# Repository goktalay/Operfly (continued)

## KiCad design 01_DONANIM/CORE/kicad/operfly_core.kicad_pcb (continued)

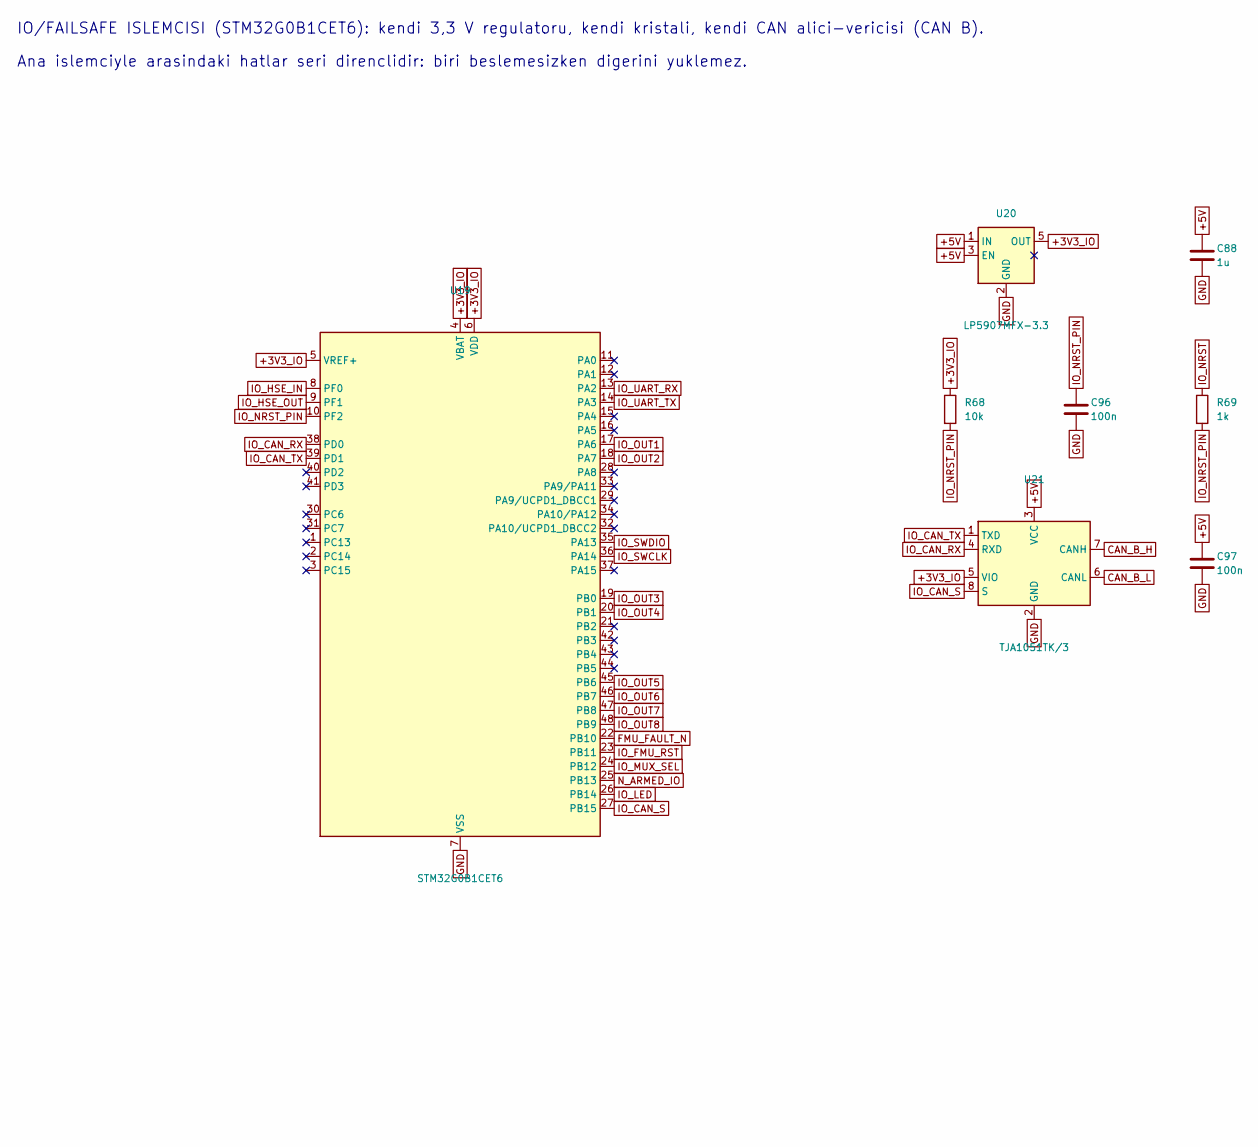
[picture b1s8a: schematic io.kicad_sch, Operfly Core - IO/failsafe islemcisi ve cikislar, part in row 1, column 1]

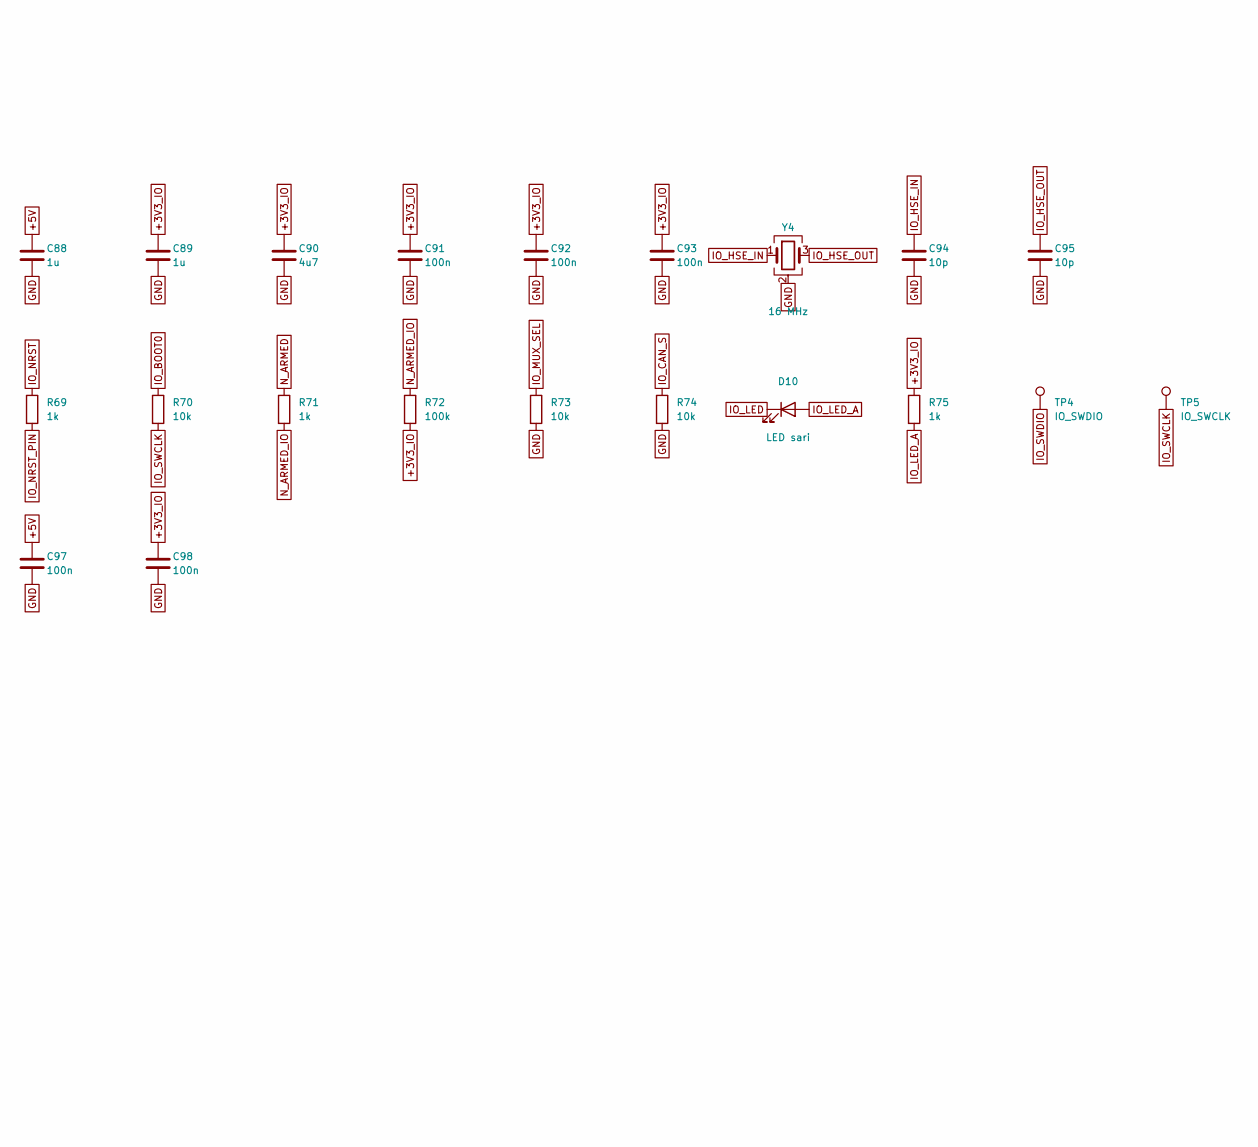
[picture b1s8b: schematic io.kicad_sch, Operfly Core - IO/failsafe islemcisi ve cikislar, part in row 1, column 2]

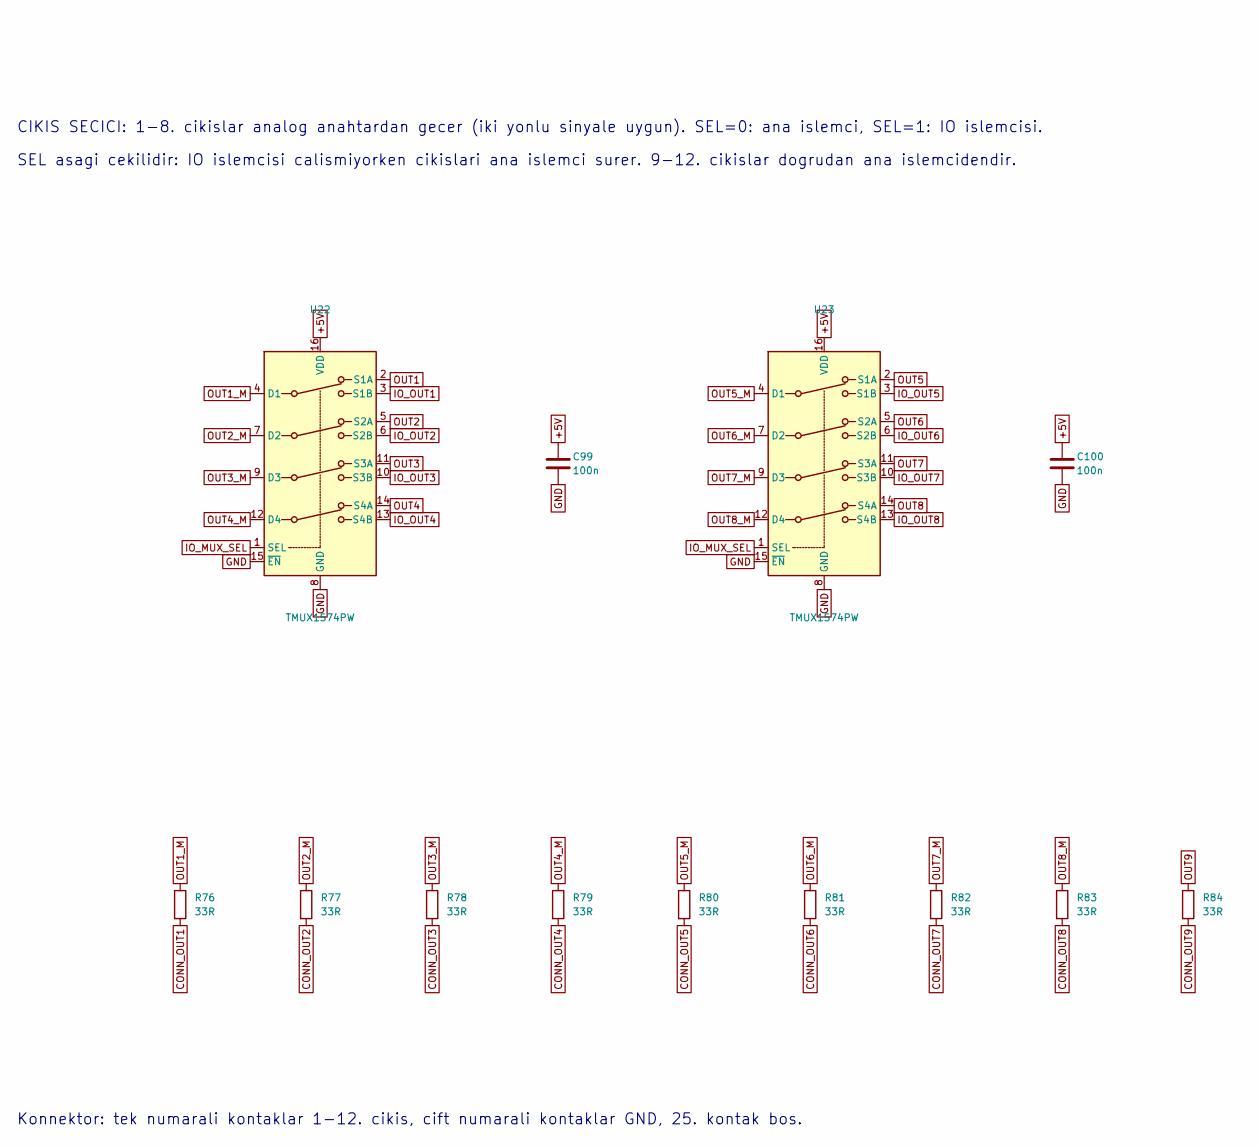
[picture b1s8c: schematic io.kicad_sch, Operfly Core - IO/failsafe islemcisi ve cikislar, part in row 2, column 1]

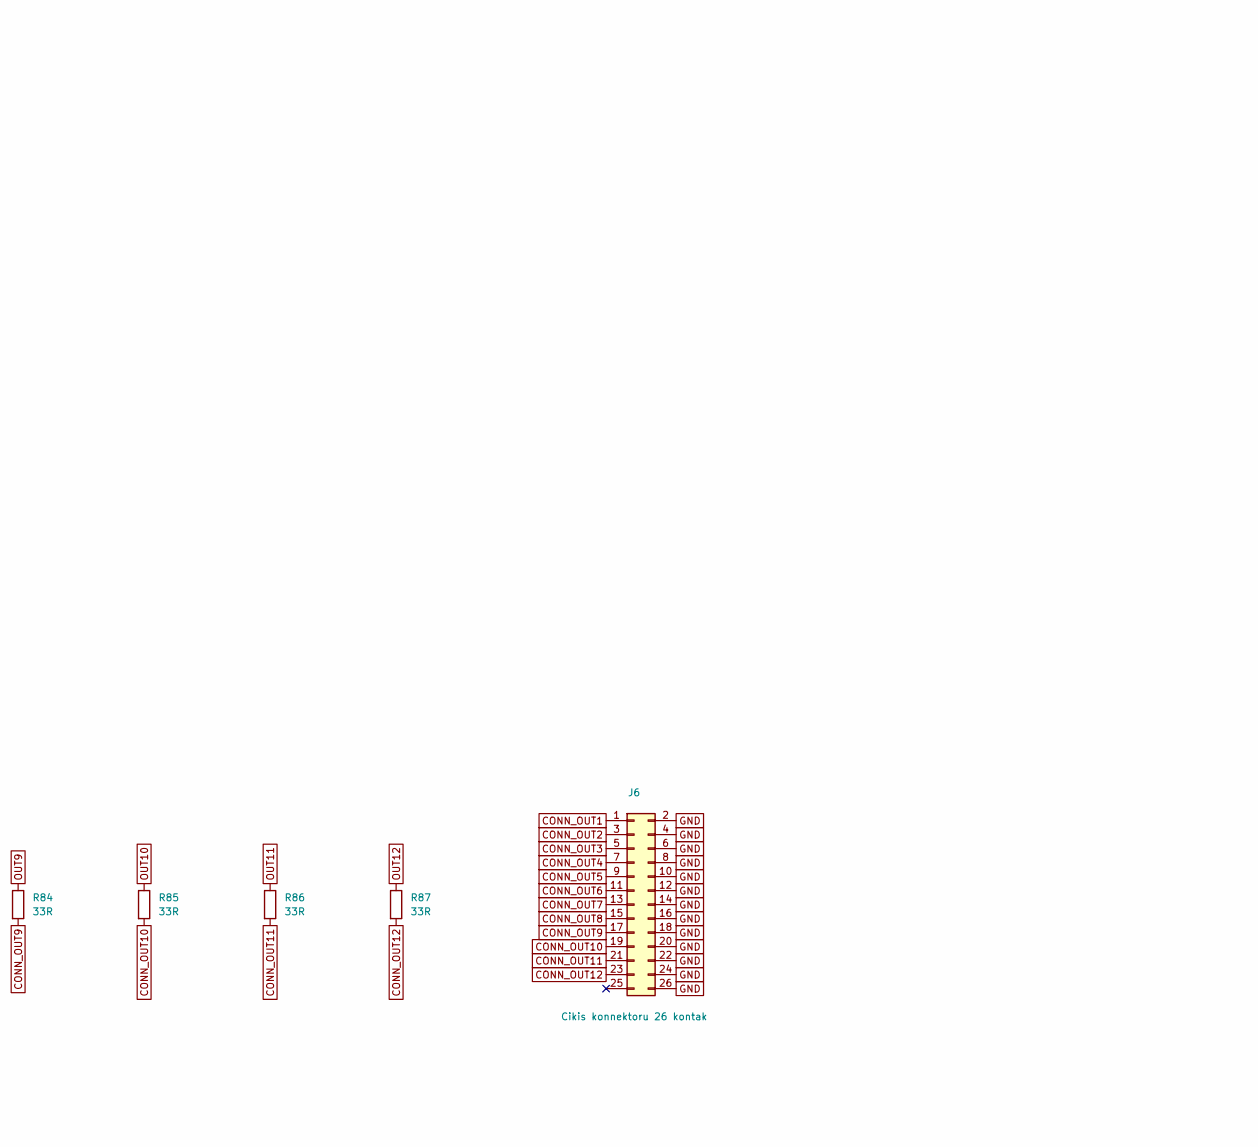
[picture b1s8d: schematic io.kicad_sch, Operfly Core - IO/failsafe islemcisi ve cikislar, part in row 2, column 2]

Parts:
C88, C89: 1u; C_0402_1005Metric
C90: 4u7; C_0603_1608Metric
C91, C92, C93, C96, C97, C98, C99, C100: 100n; C_0402_1005Metric
C94, C95: 10p; C_0402_1005Metric
D10: LED sari; LED_0603_1608Metric
J6: Cikis konnektoru 26 kontak; Harwin_Gecko_G125-MS12605M2P_2x13_P1.25mm_Vertical
R68, R70, R73, R74: 10k; R_0402_1005Metric
R69, R71, R75: 1k; R_0402_1005Metric
R72: 100k; R_0402_1005Metric
R76, R77, R78, R79, R80, R81, R82, R83, R84, R85, R86, R87: 33R; R_0402_1005Metric
TP4: IO_SWDIO; TestPoint_Pad_D1.0mm
TP5: IO_SWCLK; TestPoint_Pad_D1.0mm
U19: STM32G0B1CET6; LQFP-48_7x7mm_P0.5mm
U20: LP5907MFX-3.3; SOT-23-5
U21: TJA1051TK/3; HVSON-8-1EP_3x3mm_P0.65mm_EP1.6x2.4mm
U22, U23: TMUX1574PW; TSSOP-16_4.4x5mm_P0.65mm
Y4: 16 MHz; Crystal_SMD_3225-4Pin_3.2x2.5mm

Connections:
+3V3_IO: C89.1, C90.1, C91.1, C92.1, C93.1, C98.1, R68.1, R72.2, R75.1, U19.4 (VBAT), U19.5 (VREF+), U19.6 (VDD), U20.5 (OUT), U21.5 (VIO); also elsewhere on the board
+5V: C88.1, C97.1, C99.1, C100.1, U20.1 (IN), U20.3 (EN), U21.3 (VCC), U22.16 (VDD), U23.16 (VDD); also elsewhere on the board
CAN_B_H: U21.7 (CANH); also elsewhere on the board
CAN_B_L: U21.6 (CANL); also elsewhere on the board
CONN_OUT1: J6.1, R76.2
CONN_OUT2: J6.3, R77.2
CONN_OUT3: J6.5, R78.2
CONN_OUT4: J6.7, R79.2
CONN_OUT5: J6.9, R80.2
CONN_OUT6: J6.11, R81.2
CONN_OUT7: J6.13, R82.2
CONN_OUT8: J6.15, R83.2
CONN_OUT9: J6.17, R84.2
CONN_OUT10: J6.19, R85.2
CONN_OUT11: J6.21, R86.2
CONN_OUT12: J6.23, R87.2
FMU_FAULT_N: U19.22 (PB10); also elsewhere on the board
GND: C88.2, C89.2, C90.2, C91.2, C92.2, C93.2, C94.2, C95.2, C96.2, C97.2, C98.2, C99.2, C100.2, J6.2, J6.4, J6.6, J6.8, J6.10, J6.12, J6.14, J6.16, J6.18, J6.20, J6.22, J6.24, J6.26, R73.2, R74.2, U19.7 (VSS), U20.2 (GND), U21.2 (GND), U21.9 (GND), U22.8 (GND), U22.15 (~EN), U23.8 (GND), U23.15 (~EN), Y4.2 (G), Y4.4 (G); also elsewhere on the board
IO_BOOT0: R70.1; also elsewhere on the board
IO_CAN_RX: U19.38 (PD0), U21.4 (RXD)
IO_CAN_S: R74.1, U19.27 (PB15), U21.8 (S)
IO_CAN_TX: U19.39 (PD1), U21.1 (TXD)
IO_FMU_RST: U19.23 (PB11); also elsewhere on the board
IO_HSE_IN: C94.1, U19.8 (PF0), Y4.1
IO_HSE_OUT: C95.1, U19.9 (PF1), Y4.3
IO_LED: D10.1 (K), U19.26 (PB14)
IO_LED_A: D10.2 (A), R75.2
IO_MUX_SEL: R73.1, U19.24 (PB12), U22.1 (SEL), U23.1 (SEL)
IO_NRST: R69.1; also elsewhere on the board
IO_NRST_PIN: C96.1, R68.2, R69.2, U19.10 (PF2)
IO_OUT1: U19.17 (PA6), U22.3 (S1B)
IO_OUT2: U19.18 (PA7), U22.6 (S2B)
IO_OUT3: U19.19 (PB0), U22.10 (S3B)
IO_OUT4: U19.20 (PB1), U22.13 (S4B)
IO_OUT5: U19.45 (PB6), U23.3 (S1B)
IO_OUT6: U19.46 (PB7), U23.6 (S2B)
IO_OUT7: U19.47 (PB8), U23.10 (S3B)
IO_OUT8: U19.48 (PB9), U23.13 (S4B)
IO_SWCLK: R70.2, TP5.1, U19.36 (PA14)
IO_SWDIO: TP4.1, U19.35 (PA13)
IO_UART_RX: U19.13 (PA2); also elsewhere on the board
IO_UART_TX: U19.14 (PA3); also elsewhere on the board
N_ARMED: R71.1; also elsewhere on the board
N_ARMED_IO: R71.2, R72.1, U19.25 (PB13)
OUT1: U22.2 (S1A); also elsewhere on the board
OUT1_M: R76.1, U22.4 (D1)
OUT2: U22.5 (S2A); also elsewhere on the board
OUT2_M: R77.1, U22.7 (D2)
OUT3: U22.11 (S3A); also elsewhere on the board
OUT3_M: R78.1, U22.9 (D3)
OUT4: U22.14 (S4A); also elsewhere on the board
OUT4_M: R79.1, U22.12 (D4)
OUT5: U23.2 (S1A); also elsewhere on the board
OUT5_M: R80.1, U23.4 (D1)
OUT6: U23.5 (S2A); also elsewhere on the board
OUT6_M: R81.1, U23.7 (D2)
OUT7: U23.11 (S3A); also elsewhere on the board
OUT7_M: R82.1, U23.9 (D3)
OUT8: U23.14 (S4A); also elsewhere on the board
OUT8_M: R83.1, U23.12 (D4)
OUT9: R84.1; also elsewhere on the board
OUT10: R85.1; also elsewhere on the board
OUT11: R86.1; also elsewhere on the board
OUT12: R87.1; also elsewhere on the board

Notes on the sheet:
Ana islemciyle arasindaki hatlar seri direnclidir: biri beslemesizken digerini yuklemez.
CIKIS SECICI: 1-8. cikislar analog anahtardan gecer (iki yonlu sinyale uygun). SEL=0: ana islemci, SEL=1: IO islemcisi.
IO/FAILSAFE ISLEMCISI (STM32G0B1CET6): kendi 3,3 V regulatoru, kendi kristali, kendi CAN alici-vericisi (CAN B).
SEL asagi cekilidir: IO islemcisi calismiyorken cikislari ana islemci surer. 9-12. cikislar dogrudan ana islemcidendir.
Konnektor: tek numarali kontaklar 1-12. cikis, cift numarali kontaklar GND, 25. kontak bos.

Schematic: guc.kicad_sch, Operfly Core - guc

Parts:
C1, C3, C7: 10u 50V; C_1206_3216Metric
C2: 100n 50V; C_0603_1608Metric
C4, C8, C18, C20, C21, C22, C23, C24: 100n; C_0402_1005Metric
C5, C6, C9, C10: 22u 16V; C_1206_3216Metric
C11, C12, C13, C14, C15, C16, C17, C19: 1u; C_0402_1005Metric
D1, D2: B360A (60 V, 3 A); D_SMA
D3: SMBJ18A; D_SMB
FB1: BLM18PG221; L_0603_1608Metric
L1: 4u7 XAL4020-472; L_Coilcraft_XAL4020-XXX
L2: 3u3 XAL4020-332; L_Coilcraft_XAL4020-XXX
R1, R2, R3, R4, R5, R8: 100k; R_0402_1005Metric
R6: 10R; R_0402_1005Metric
R7: 0R; R_0402_1005Metric
R9, R10, R11, R12, R13, R14: 10k; R_0402_1005Metric
R15: 18k; R_0402_1005Metric
U2: AP63205QWU; TSOT-23-6
U3: AP63203QWU; TSOT-23-6
U4, U5, U6: LP5907MFX-3.3; SOT-23-5

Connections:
+3V3: C9.1, C10.1, FB1.1, L2.2, R7.1, U3.1 (FB); also elsewhere on the board
+3V3A: C17.1, C18.1, FB1.2, R6.1; also elsewhere on the board
+3V3_S1: C12.1, R12.1, U4.5 (OUT); also elsewhere on the board
+3V3_S2: C14.1, U5.5 (OUT); also elsewhere on the board
+3V3_S3: C16.1, U6.5 (OUT); also elsewhere on the board
+5V: C5.1, C6.1, C11.1, C13.1, C15.1, L1.2, R10.1, R14.1, U2.1 (FB), U4.1 (IN), U5.1 (IN), U6.1 (IN); also elsewhere on the board
+12V_BUS1: D1.2 (A); also elsewhere on the board
+12V_BUS2: D2.2 (A); also elsewhere on the board
+12V_IN: C1.1, C2.1, C3.1, C7.1, D1.1 (K), D2.1 (K), D3.1 (A1), R1.1, R2.1, R8.1, U2.3 (IN), U3.3 (IN); also elsewhere on the board
BST_3V3: C8.1, U3.6 (BST)
BST_5V: C4.1, U2.6 (BST)
EN_3V3: R2.2, U3.2 (EN)
EN_5V: R1.2, U2.2 (EN)
GND: C1.2, C2.2, C3.2, C5.2, C6.2, C7.2, C9.2, C10.2, C11.2, C12.2, C13.2, C14.2, C15.2, C16.2, C17.2, C18.2, C19.2, C20.2, C21.2, C22.2, C23.2, C24.2, D3.2 (A2), R3.2, R4.2, R5.2, R9.2, R11.2, R13.2, R15.2, U2.4 (GND), U3.4 (GND), U4.2 (GND), U5.2 (GND), U6.2 (GND); also elsewhere on the board
PGOOD_5V: R14.2, R15.1; also elsewhere on the board
SENS1_EN: R3.1, U4.3 (EN); also elsewhere on the board
SENS2_EN: R4.1, U5.3 (EN); also elsewhere on the board
SENS3_EN: R5.1, U6.3 (EN); also elsewhere on the board
SW_3V3: C8.2, L2.1, U3.5 (SW)
SW_5V: C4.2, L1.1, U2.5 (SW)
V3V3_SENS: C24.1, R12.2, R13.1; also elsewhere on the board
V5_SENS: C23.1, R10.2, R11.1; also elsewhere on the board
V12_BUS_SENS: C22.1, R8.2, R9.1; also elsewhere on the board
VBAT: C21.1, R7.2; also elsewhere on the board
VREF: C19.1, C20.1, R6.2; also elsewhere on the board

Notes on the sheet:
GIRIS: iki omurga portu diyotla birlestirilir (+12V_IN). Asiri gerilim diyotu 18 V.
ANALOG BESLEME ve REFERANS: +3V3A ferrit uzerinden, VREF 10 ohm uzerinden. VBAT +3V3'e bagli (yedek pil yok).
SENSOR BESLEMELERI: her IMU icin ayri, islemciden acilip kapatilan dusuk gurultulu regulator (LP5907-3.3).
3,3 V: AP63203 (sabit 3,3 V, 2 A). L 3,3 uH, cikis 2 x 22 uF. 12 V'tan dogrudan beslenir.
OLCUM BOLUCULERI: 12 V icin 11:1, 5 V ve sensor beslemesi icin 2:1. PGOOD_5V: 5 V varken yuksek.
5 V: AP63205 (sabit 5 V, 2 A, 1,1 MHz). Degerler uretici ornek devresinden: L 4,7 uH, cikis 2 x 22 uF.

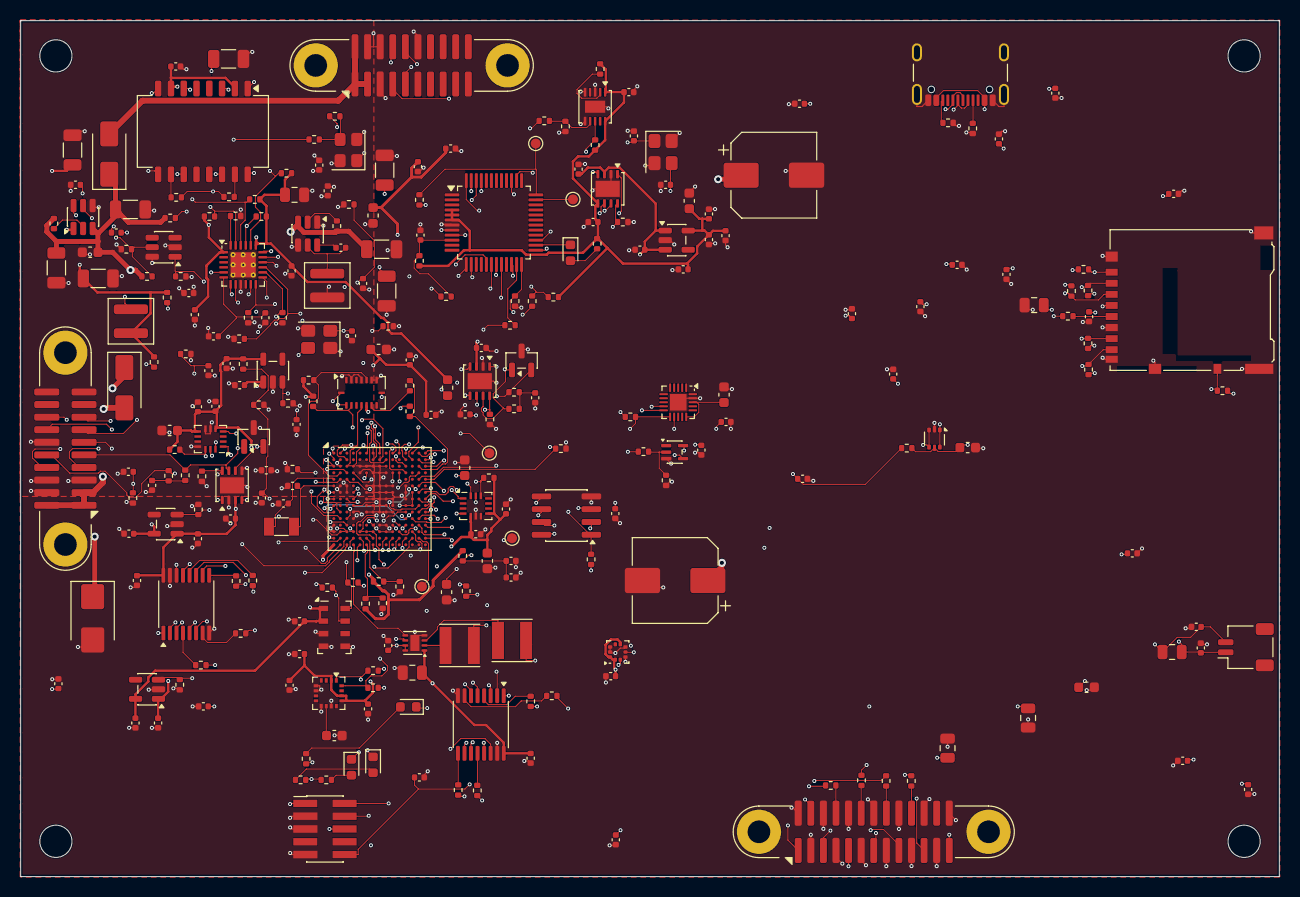
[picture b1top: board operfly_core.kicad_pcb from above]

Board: 6 copper layers, 125.0 x 85.0 mm, 268 parts (0 on the bottom side), 204 nets.

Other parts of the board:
H1, H2, H3, H4: M3; MountingHole_3.2mm_M3

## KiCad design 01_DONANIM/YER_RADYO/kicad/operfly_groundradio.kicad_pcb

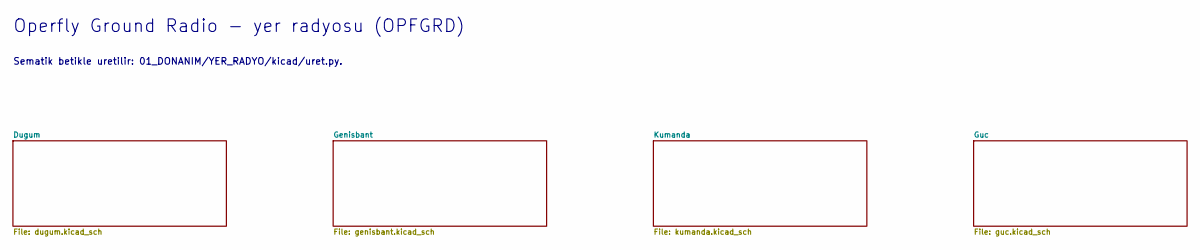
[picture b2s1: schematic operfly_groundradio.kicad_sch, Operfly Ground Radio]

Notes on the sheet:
Operfly Ground Radio - yer radyosu (OPFGRD)
Sematik betikle uretilir: 01_DONANIM/YER_RADYO/kicad/uret.py.

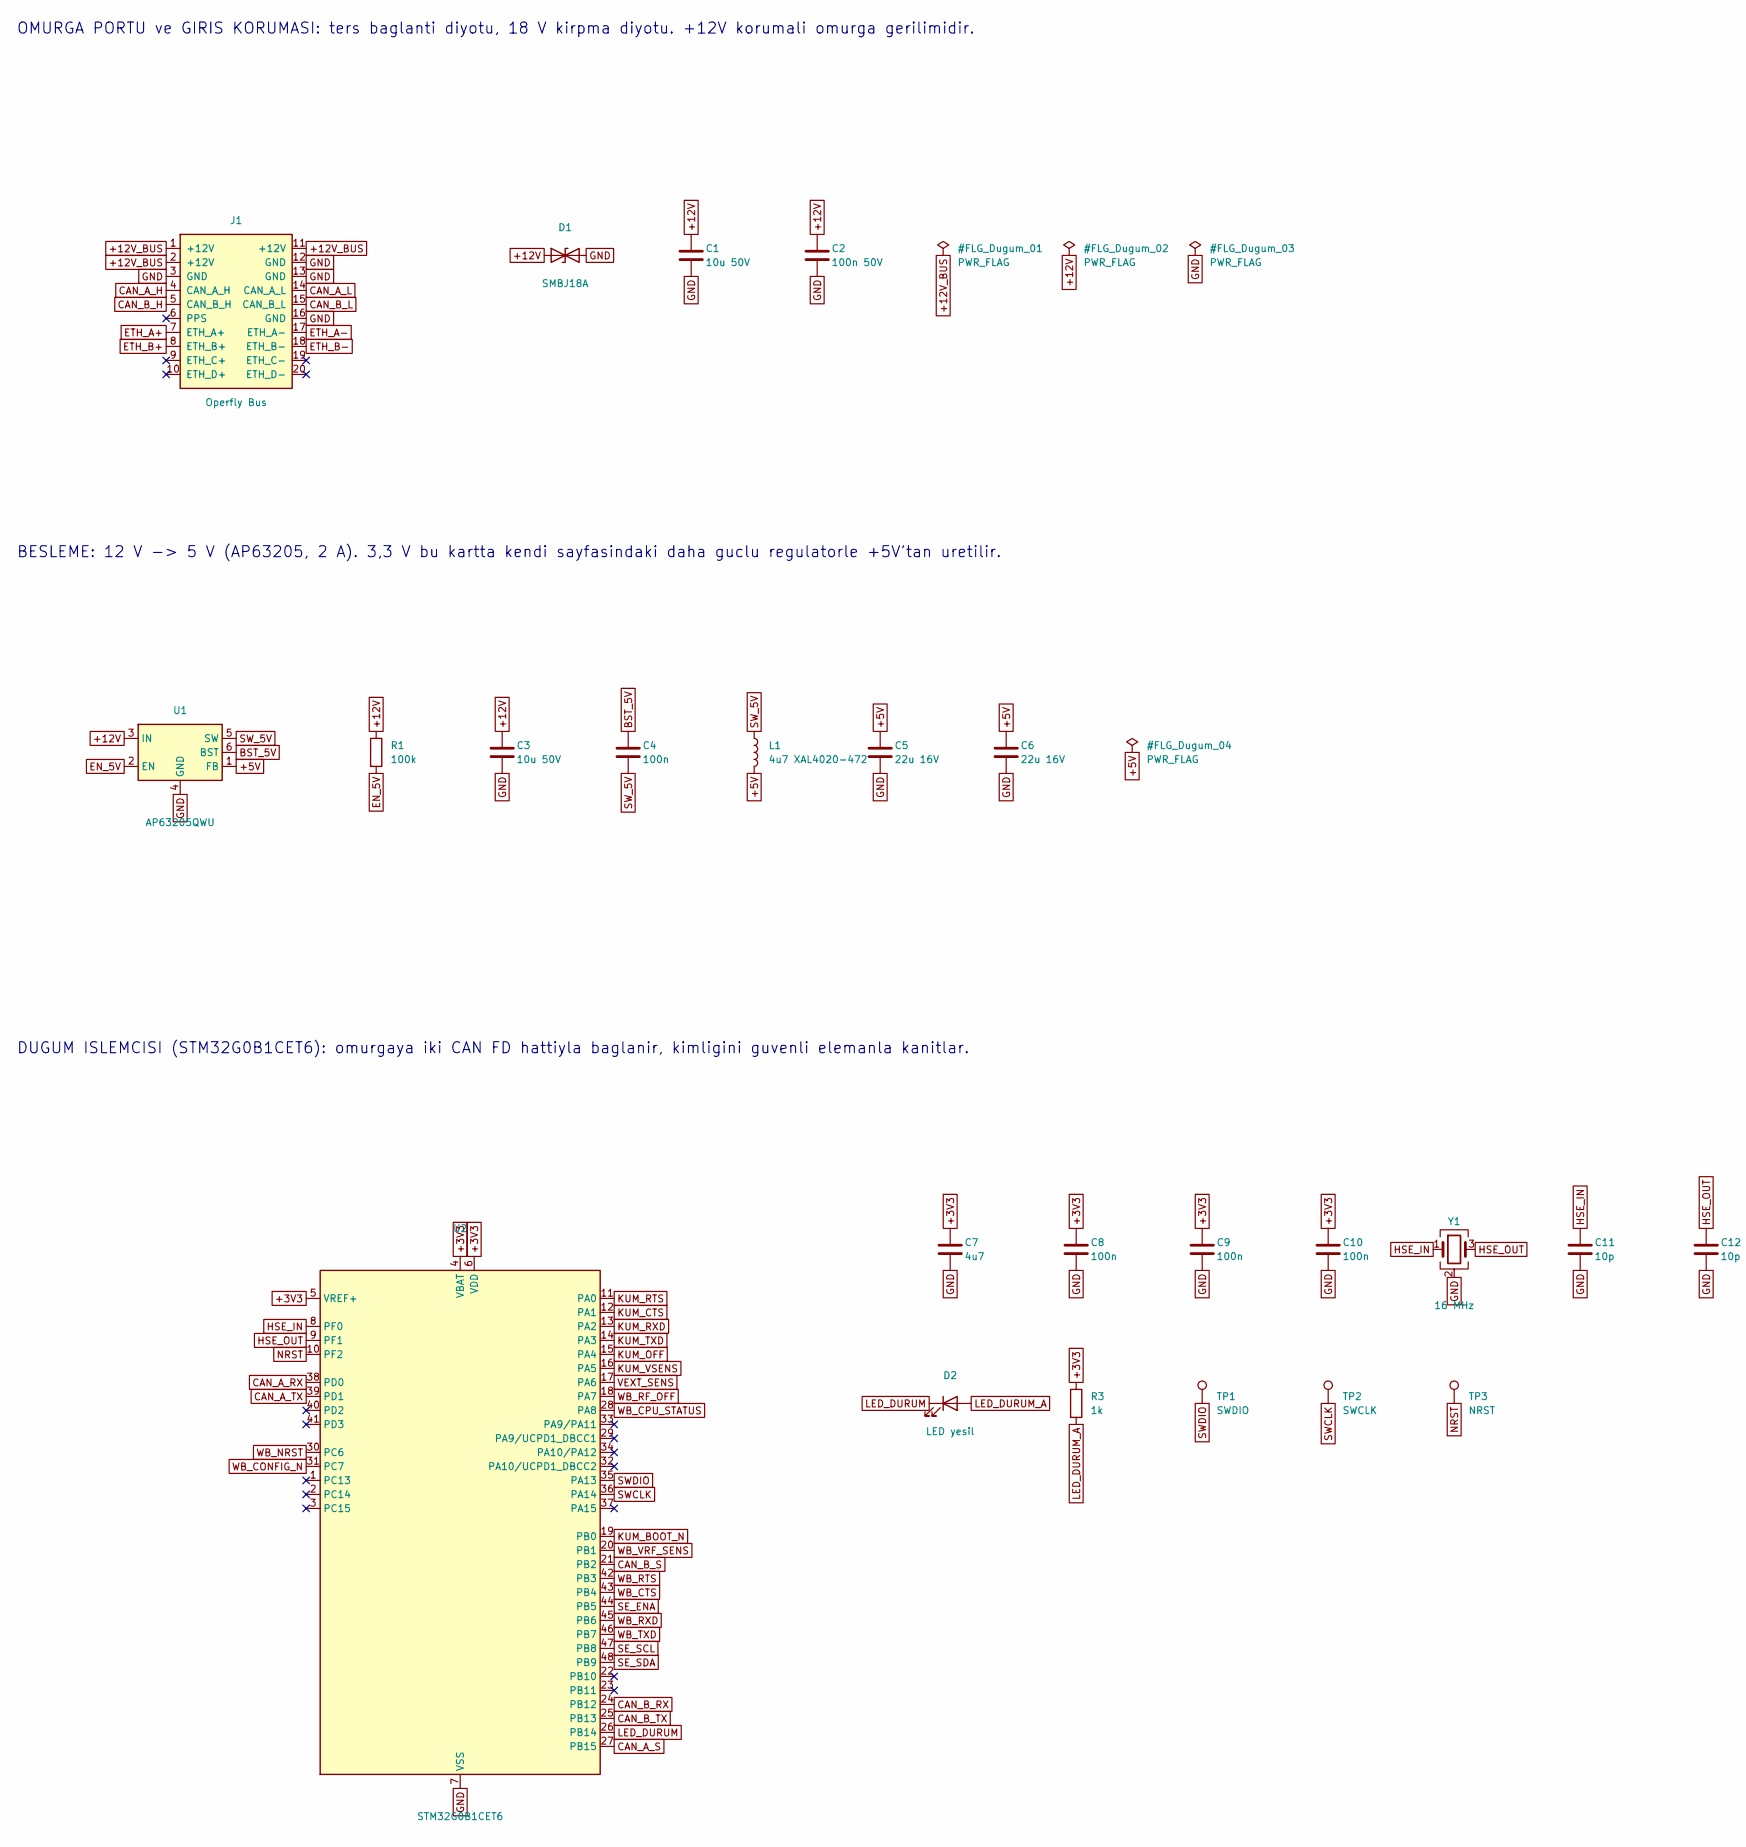
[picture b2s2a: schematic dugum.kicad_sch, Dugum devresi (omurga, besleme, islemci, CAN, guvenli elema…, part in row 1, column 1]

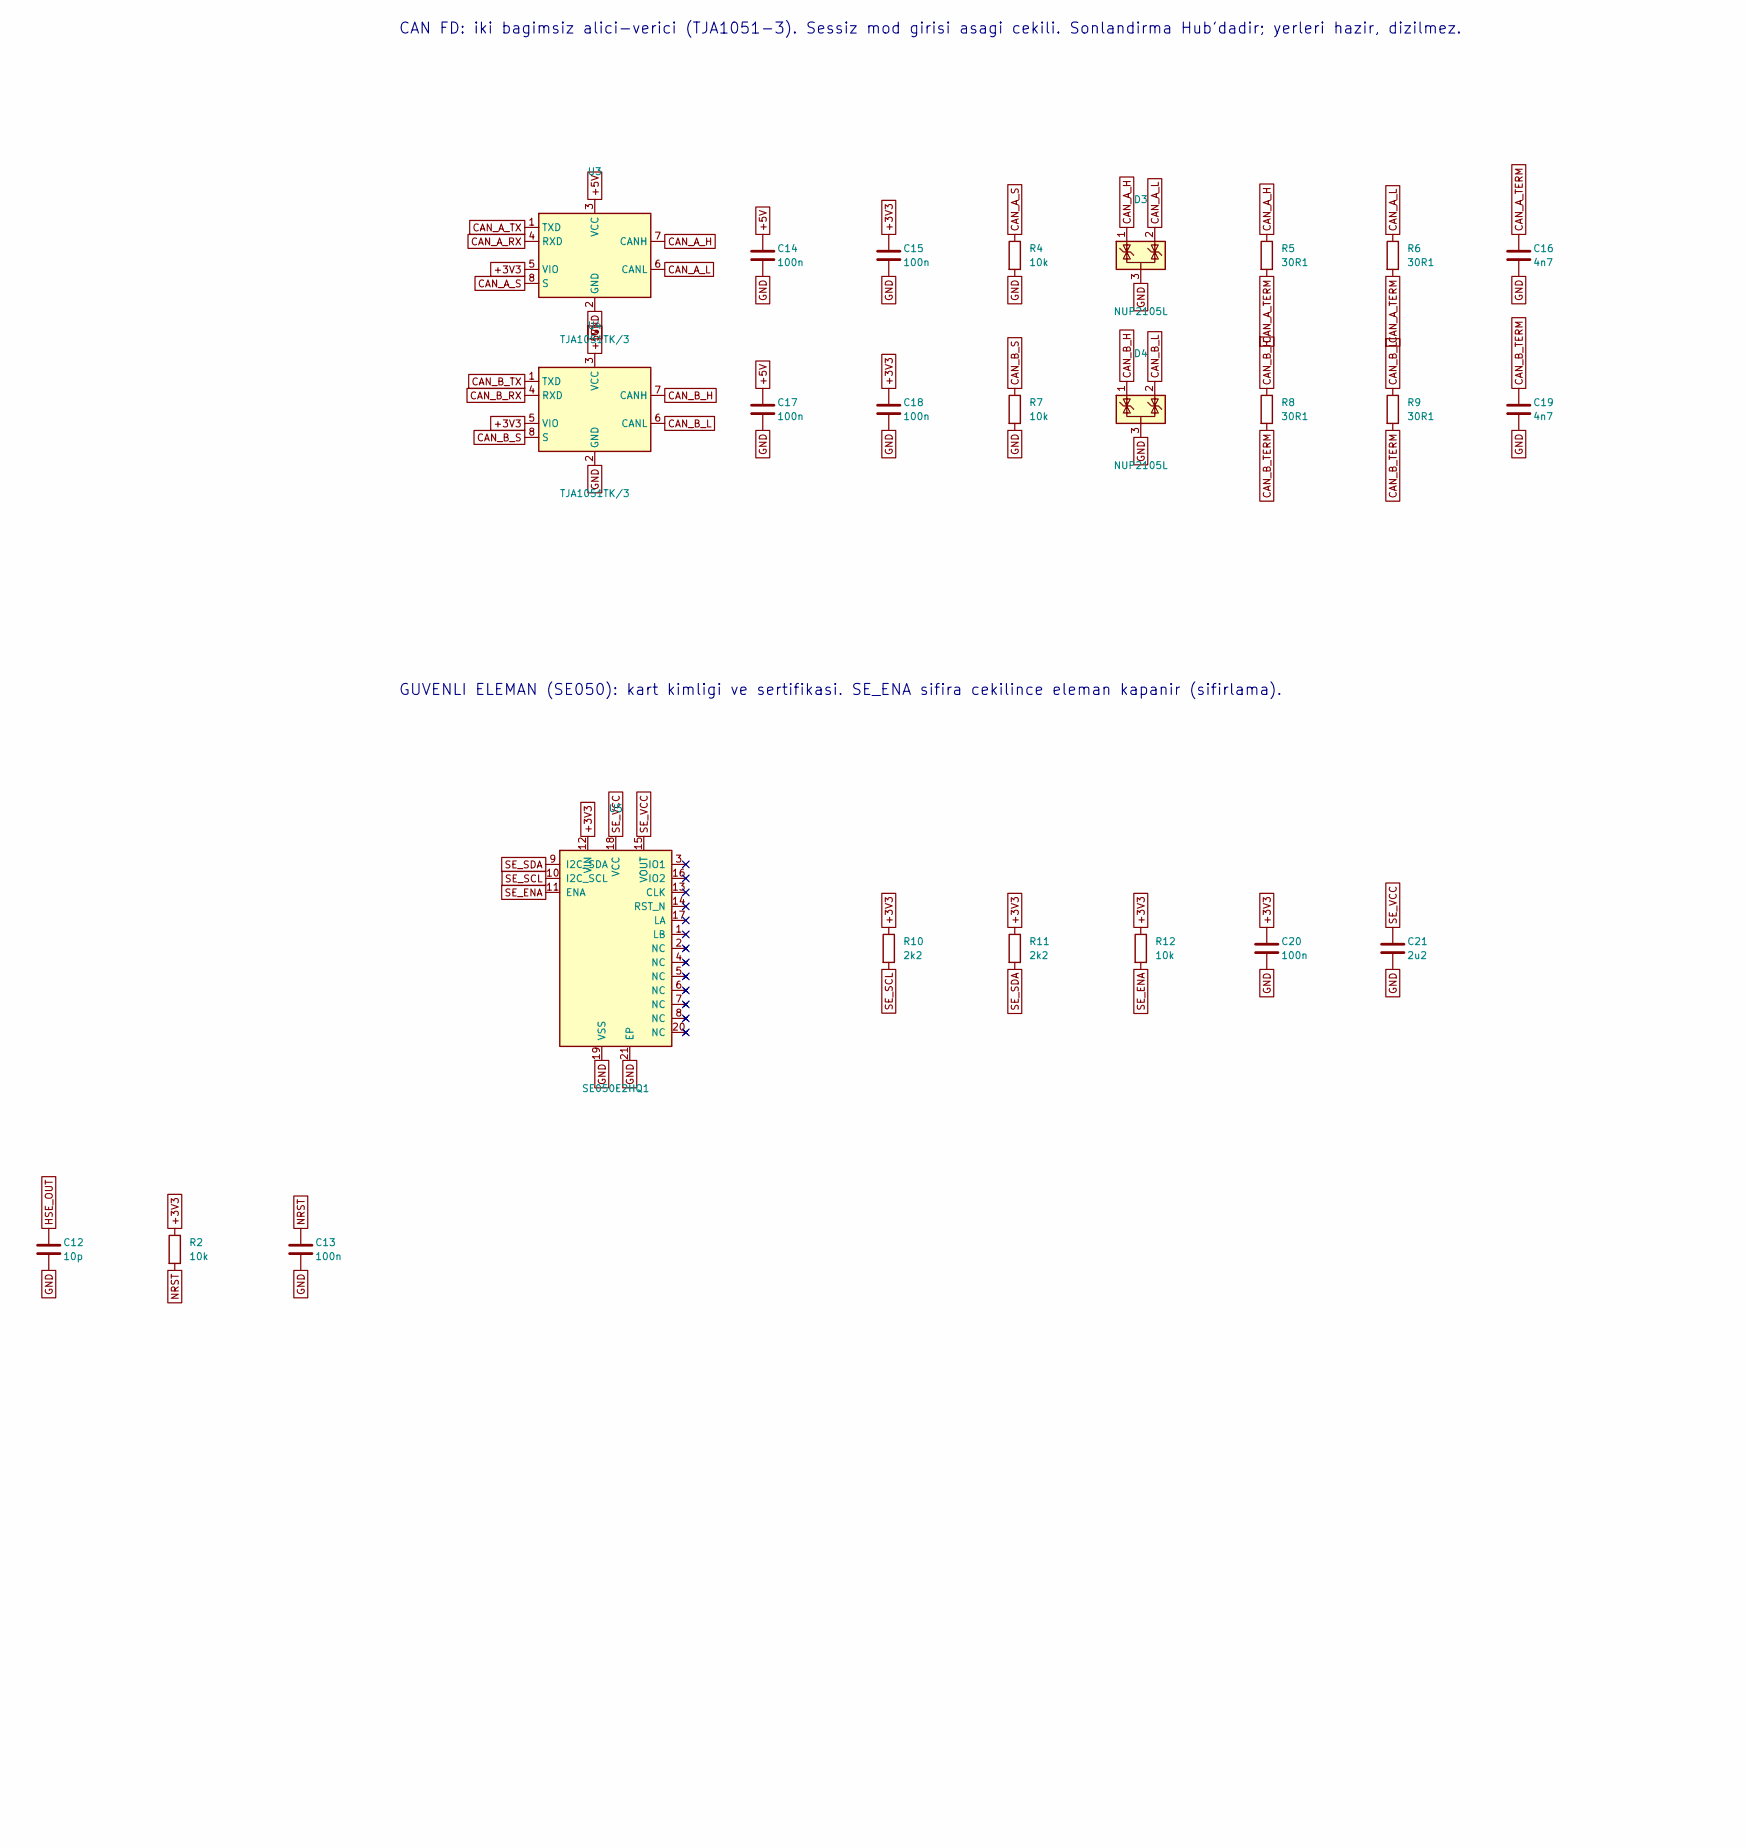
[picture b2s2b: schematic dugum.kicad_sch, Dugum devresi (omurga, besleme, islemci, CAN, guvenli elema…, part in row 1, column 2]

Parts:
C1, C3: 10u 50V; C_1206_3216Metric
C2: 100n 50V; C_0603_1608Metric
C4, C8, C9, C10, C13, C14, C15, C17, C18, C20: 100n; C_0402_1005Metric
C5, C6: 22u 16V; C_1206_3216Metric
C7: 4u7; C_0603_1608Metric
C11, C12: 10p; C_0402_1005Metric
C16, C19: 4n7; C_0402_1005Metric
C21: 2u2; C_0603_1608Metric
D1: SMBJ18A; D_SMB
D2: LED yesil; LED_0603_1608Metric
D3, D4: NUP2105L; SOT-23
J1: Operfly Bus; Harwin_Gecko_G125-MS12005M2P_2x10_P1.25mm_Vertical
L1: 4u7 XAL4020-472; L_Coilcraft_XAL4020-XXX
R1: 100k; R_0402_1005Metric
R2, R4, R7, R12: 10k; R_0402_1005Metric
R3: 1k; R_0402_1005Metric
R5, R6, R8, R9: 30R1; R_0402_1005Metric
R10, R11: 2k2; R_0402_1005Metric
TP1: SWDIO; TestPoint_Pad_D1.0mm
TP2: SWCLK; TestPoint_Pad_D1.0mm
TP3: NRST; TestPoint_Pad_D1.0mm
U1: AP63205QWU; TSOT-23-6
U2: STM32G0B1CET6; LQFP-48_7x7mm_P0.5mm
U3, U4: TJA1051TK/3; HVSON-8-1EP_3x3mm_P0.65mm_EP1.6x2.4mm
U5: SE050E2HQ1; QFN-20-1EP_3x3mm_P0.4mm_EP1.65x1.65mm
Y1: 16 MHz; Crystal_SMD_3225-4Pin_3.2x2.5mm

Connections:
+3V3: C7.1, C8.1, C9.1, C10.1, C15.1, C18.1, C20.1, R2.1, R3.1, R10.1, R11.1, R12.1, U2.4 (VBAT), U2.5 (VREF+), U2.6 (VDD), U3.5 (VIO), U4.5 (VIO), U5.12 (VIN); also elsewhere on the board
+5V: C5.1, C6.1, C14.1, C17.1, L1.2, U1.1 (FB), U3.3 (VCC), U4.3 (VCC)
+12V: C1.1, C2.1, C3.1, D1.1 (A1), R1.1, U1.3 (IN); also elsewhere on the board
+12V_BUS: J1.1 (+12V), J1.2 (+12V), J1.11 (+12V); also elsewhere on the board
BST_5V: C4.1, U1.6 (BST)
CAN_A_H: D3.1 (K), J1.4 (CAN_A_H), R5.1, U3.7 (CANH); also elsewhere on the board
CAN_A_L: D3.2 (K), J1.14 (CAN_A_L), R6.1, U3.6 (CANL); also elsewhere on the board
CAN_A_RX: U2.38 (PD0), U3.4 (RXD)
CAN_A_S: R4.1, U2.27 (PB15), U3.8 (S)
CAN_A_TERM: C16.1, R5.2, R6.2
CAN_A_TX: U2.39 (PD1), U3.1 (TXD)
CAN_B_H: D4.1 (K), J1.5 (CAN_B_H), R8.1, U4.7 (CANH); also elsewhere on the board
CAN_B_L: D4.2 (K), J1.15 (CAN_B_L), R9.1, U4.6 (CANL); also elsewhere on the board
CAN_B_RX: U2.24 (PB12), U4.4 (RXD)
CAN_B_S: R7.1, U2.21 (PB2), U4.8 (S)
CAN_B_TERM: C19.1, R8.2, R9.2
CAN_B_TX: U2.25 (PB13), U4.1 (TXD)
EN_5V: R1.2, U1.2 (EN)
ETH_A+: J1.7 (ETH_A+); also elsewhere on the board
ETH_A-: J1.17 (ETH_A-); also elsewhere on the board
ETH_B+: J1.8 (ETH_B+); also elsewhere on the board
ETH_B-: J1.18 (ETH_B-); also elsewhere on the board
GND: C1.2, C2.2, C3.2, C5.2, C6.2, C7.2, C8.2, C9.2, C10.2, C11.2, C12.2, C13.2, C14.2, C15.2, C16.2, C17.2, C18.2, C19.2, C20.2, C21.2, D1.2 (A2), D3.3 (A), D4.3 (A), J1.3 (GND), J1.12 (GND), J1.13 (GND), J1.16 (GND), R4.2, R7.2, U1.4 (GND), U2.7 (VSS), U3.2 (GND), U3.9 (GND), U4.2 (GND), U4.9 (GND), U5.19 (VSS), U5.21 (EP), Y1.2 (G), Y1.4 (G); also elsewhere on the board
HSE_IN: C11.1, U2.8 (PF0), Y1.1
HSE_OUT: C12.1, U2.9 (PF1), Y1.3
KUM_BOOT_N: U2.19 (PB0); also elsewhere on the board
KUM_CTS: U2.12 (PA1); also elsewhere on the board
KUM_OFF: U2.15 (PA4); also elsewhere on the board
KUM_RTS: U2.11 (PA0); also elsewhere on the board
KUM_RXD: U2.13 (PA2); also elsewhere on the board
KUM_TXD: U2.14 (PA3); also elsewhere on the board
KUM_VSENS: U2.16 (PA5); also elsewhere on the board
LED_DURUM: D2.1 (K), U2.26 (PB14)
LED_DURUM_A: D2.2 (A), R3.2
NRST: C13.1, R2.2, TP3.1, U2.10 (PF2)
SE_ENA: R12.2, U2.44 (PB5), U5.11 (ENA)
SE_SCL: R10.2, U2.47 (PB8), U5.10 (I2C_SCL)
SE_SDA: R11.2, U2.48 (PB9), U5.9 (I2C_SDA)
SE_VCC: C21.1, U5.15 (VOUT), U5.18 (VCC)
SWCLK: TP2.1, U2.36 (PA14)
SWDIO: TP1.1, U2.35 (PA13)
SW_5V: C4.2, L1.1, U1.5 (SW)
VEXT_SENS: U2.17 (PA6); also elsewhere on the board
WB_CONFIG_N: U2.31 (PC7); also elsewhere on the board
WB_CPU_STATUS: U2.28 (PA8); also elsewhere on the board
WB_CTS: U2.43 (PB4); also elsewhere on the board
WB_NRST: U2.30 (PC6); also elsewhere on the board
WB_RF_OFF: U2.18 (PA7); also elsewhere on the board
WB_RTS: U2.42 (PB3); also elsewhere on the board
WB_RXD: U2.45 (PB6); also elsewhere on the board
WB_TXD: U2.46 (PB7); also elsewhere on the board
WB_VRF_SENS: U2.20 (PB1); also elsewhere on the board

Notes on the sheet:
CAN FD: iki bagimsiz alici-verici (TJA1051-3). Sessiz mod girisi asagi cekili. Sonlandirma Hub'dadir; yerleri hazir, dizilmez.
BESLEME: 12 V -> 5 V (AP63205, 2 A). 3,3 V bu kartta kendi sayfasindaki daha guclu regulatorle +5V'tan uretilir.
DUGUM ISLEMCISI (STM32G0B1CET6): omurgaya iki CAN FD hattiyla baglanir, kimligini guvenli elemanla kanitlar.
GUVENLI ELEMAN (SE050): kart kimligi ve sertifikasi. SE_ENA sifira cekilince eleman kapanir (sifirlama).
OMURGA PORTU ve GIRIS KORUMASI: ters baglanti diyotu, 18 V kirpma diyotu. +12V korumali omurga gerilimidir.
